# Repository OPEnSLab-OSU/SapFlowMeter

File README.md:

# SapFlowMeter

A sap flow meter measures the velocity of the sap in a tree. This is a useful indicator of the tree's health, and can provide valuable feedback for irrigation and water management.

Our meter here uses the Heat Ratio Method, where it applies a heat pulse into the sapwood, and measures the temperature of the sapwood both above and below the heater.

Currently we have designed flexible PCB probes, and we are testing our sap flow measurements in a tree against empirical water consumption measurements and a commercial sapflow probe.

## Libraries required:
- [SdFat](https://github.com/greiman/SdFat "SdFat")
- [OPEnS RTC](https://github.com/OPEnSLab-OSU/OPEnS_RTC "OPEnS_RTC")
- [Adafruit MAX31865](https://github.com/adafruit/Adafruit_MAX31865 "Adafruit MAX31865")
- [Low-Power](https://github.com/rocketscream/Low-Power "Low-Power")
- [Protothreads](https://github.com/P4SSER8Y/ProtoThreadsForArduino)
- [DSPlite](https://github.com/kamocat/DSPlite)
- [RadioHead](https://github.com/adafruit/RadioHead)
- [ArduinoJSON](https://github.com/bblanchon/ArduinoJson)
- [FeatherFault](https://github.com/OPEnSLab-OSU/FeatherFault)
- [ASF core](https://github.com/adafruit/Adafruit_ASFcore.git) commit f6ffa8b
- [Plog](https://github.com/OPEnSLab-OSU/plog)

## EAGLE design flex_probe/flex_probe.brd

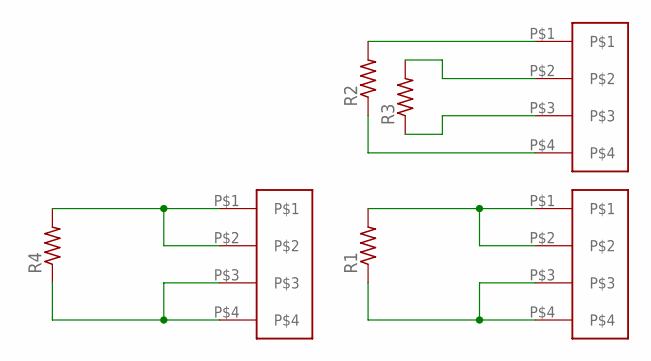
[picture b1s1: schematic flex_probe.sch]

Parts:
R1, R2, R3, R4: R-US_R0603; R0603
U$1, U$2, U$3: CONN_1X4; 4PAD

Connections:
unnamed: R1.2, U$1.P$1, U$1.P$2
unnamed: R1.1, U$1.P$3, U$1.P$4
unnamed: R2.1, U$2.P$4
unnamed: R3.2, U$2.P$2
unnamed: R3.1, U$2.P$3
unnamed: R2.2, U$2.P$1
unnamed: R4.2, U$3.P$1, U$3.P$2
unnamed: R4.1, U$3.P$3, U$3.P$4

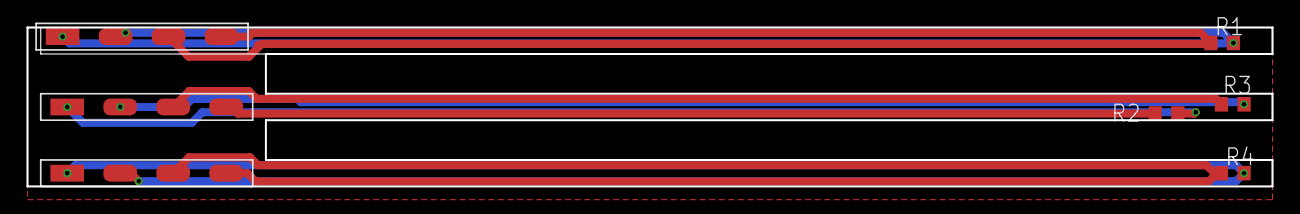
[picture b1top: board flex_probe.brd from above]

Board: 2 copper layers, 94.0 x 12.0 mm, 7 parts (0 on the bottom side), 8 nets.

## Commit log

2019-11-27 Deployed in tree 11/26/2019
    Currently testing quality of measurements and calculations.
2019-11-27 Update README.md
    Added "required libraries" list to readme
2019-11-27 Changed formula for flow calculation.
2019-11-27 Made Python script for examining data from sapflow probe
2019-11-27 Attempting to parse dates. Not working very well
2019-12-08 Made a least-squares slope finder
2019-12-08 Huge improvement in linear regression over naive slope
2019-12-08 Optimized linear regression for translation to C++
2019-12-08 Partial revert of 'optimization'.
    Numpy is much much faster than a for loop. Changed the for-loop accumulation back to a matrix dot-product.
2019-12-08 Put new calculation into a function.
    Intended to test for zeroing in on the steepest part of the slope,
    but it seemed to make slope estimates worse rather than better.
2019-12-10 Added 3rd RTD.
    Working on refactoring code to remvoe extra stuff
2019-12-26 Had to revert the changes to Adafruit's Max31965
2019-12-26 Logging weight successfully
2020-01-06 Use improved calculation to determine sapflow, and extract weight for comparison
2020-01-07 Added Adafruit's feather LoRa examples
2020-01-07 Reliable datagram over LoRa
2020-01-11 Made script to smooth the quantization error out of the weight measurement
2020-01-11 fixed discontinuities which occur during watering
2020-01-22 scaling weight to gravimetric
2020-01-31 Integrated JSON formatted LORA messages and Ethernet transmission to database
2020-02-01 Fixed issues with sapflow calculation
    - Excluded data while the heater probe is on. The heater still seems to present electrical conduction issues for the RTDs.
    - Included upper and lower slope and baseline in processed data. This is useful for determining what the issues are that are causing wonky sapflow results.
2020-02-05 Rewriting sapflow using protothreads
2020-02-06 Debugging protothreads
2020-02-06 Threading seems to work.
    Looks like the 5V line on the Hypnos failed again though
2020-02-06 Seems to be trouble with the thread spawning
2020-02-06 Fixed thread issue
    Apparently child threads should block, as yielding allows the parent to continue
2020-02-06 Forced SD card to log
    Had to flush the file every time. I think the sleep prep mechanism isn't working - maybe I should use a semaphore instead?
2020-02-06 Attempting to compartmentalize LoRa
2020-02-06 Compilation issues fixed.
    Needs testing
2020-02-06 Merged LoRa into protothreads sketch
    I sure hope it works.
2020-02-06 Demo for OPEnS lab open house
2020-02-07 Fixed measurement bug
2020-02-08 Still having issues with weight.
2020-02-09 Added Doxygen documentation
2020-02-09 Resolved Doxygen warnings
    All functions, parameters, and globals are documented
2020-02-13 Missed an end parenthesis
2020-02-16 Added maxtemp
    Disabled sleep, started sending actual time
2020-02-18 Added additional comments for debugging
2020-02-18 Modified log to open and close every time.
    Administrative changes:
    Removed elf and bin files from commit.
    Added Makefile for arduino-cli
2020-02-19 Moved location of html files
2020-02-19 Added mainpage for doxygen
2020-02-19 added main page
2020-02-19 Modified doxygen image to use relative path
2020-02-19 Testing relative image path
2020-02-19 Adding pictures
2020-02-19 Reverting to previous relative image path style
2020-02-19 Trying previous path style again
2020-02-19 Created sketch to test watchdog debugging
2020-02-19 Watchdog works, but seems to have scope issues
2020-02-19 Set watchdog to hard reset after two interrupt periods
2020-02-20 Moved variables from inside class to global scope - works now
2020-02-20 Fixed debug saving and restoring
2020-02-20 Watchdog reset works properly
2020-02-20 Added debug tags
2020-02-20 Implemented watchdog on sapflow_protothread
2020-02-20 Fixed maxtemp
2020-02-20 Started reading halt location at every wake
2020-02-21 Disabled waiting for serial
2020-02-27 Updated required libraries in README
2020-02-27 Removed extra repositories.
    Hardware design has moved to the [OPEnS Hardware Repository](https://github.com/OPEnSLab-OSU/PCB)
2020-02-27 Improved documentation
2020-02-27 Removed test project for watchdog debug
2020-02-27 Update index.html
    Fixed redirect page
2020-03-02 Added another commit in hopes that gh-pages will work
2020-03-06 Switched to FeatherFault
2020-03-07 Updated Makefile with "recover" option
2020-03-10 innitial commit - code untested
2020-03-13 Included FeatherFault in LoRa base station
2020-03-13 Removed some bulk from LoRa base station. Program is timing out during 'Ethernet.begin'
2020-03-13 Turned down the heat pulse
2020-03-13 Simplified MCP example
2020-03-13 Simplified temperature conversion.
    Lower and Heater probes seem to measure within 0.3 degrees of each other. The Upper Probe is constantly reading 0 - probably a bug in the data storage
2020-03-13 All three temperatures look correct now.
    I changed the output to show drift in millidegrees, so we can see something comparable to the measurements in a tree.
2020-03-15 Turned on 3.3 and 5v rails
2020-03-16 MCP3424 example now uses protothreads. Compiles but needs testing.
2020-03-16 Refactoring to allow multiple instances of a protothread
2020-03-16 Fixed typos
2020-03-17 Heater and Upper probes were swapped on MCP3424 example
2020-03-17 Testing multiple probes on one datalogger
    Having issues with spawned threads looping after exiting. Might need to use a rendezvous.
2020-03-17 Multiple probes working one one datalogger
2020-03-19 rhody deployment test
2020-03-19 Updated documentation
    Removed inline sources and verbatim headers
2020-03-20 Added .gitignore
2020-03-23 Fixed issue of hanging on wakeup
2020-03-24 Added jupyter notebook for examining tree data
2020-03-24 Created data folder
2020-03-25 Added Burgess HRM method
2020-03-25 Started linear regression method.
    Decided tree3.csv didn't have any data worth keeping
2020-03-26 Timer (#4)
    Implemented sleep_cycle() delay to avoid LoRa packet collisions via TDMA
2020-04-19 Using Plog for system error logging
2020-04-19 Swapped upper and lower due to hardware change
    Also added a second probe
2020-04-20 Re-enabled LoRa
    Now uses PLOG for logging messages
2020-04-25 Simplified configuration steps for multiple probes
    Sleep offset is now automatically calculated based off the maximum treeID
    Measurement threads with a treeID of 0 will now do nothing (allowing a convenient way to disable threads)
    LoRa radio switched to regular transmit/receive rather than ReliableDatagram
2020-04-30 Relaxed watchdog requirements
    Watchdog timer is increased to 4 seconds.
    Schedule now sleeps immidiately, so repeated watchdog faults shouldn't kill the battery.
    Fixed sleep.cpp to log with plog rather than cout.
2020-05-01 Tested new data from field deployment
2020-05-03 Added notes about data
2020-05-05 Added new data
2020-05-05 Moved jupyter notebooks to its own folder
2020-05-05 Inspected tree1 data
2020-06-14 Updated README.md to include Plog dependency
2021-07-30 Relaxed Watchdog
    Watchdog commented out.
2021-07-30 Remove LoRa Call
    As we are not using LoRa currently, removing the initialization and message creation and sending saves time and power.
2021-07-30 Updated Dependency
2021-07-30 Single Probe Version
    Created a version made for use with a single probe, this is what is currently deployed in the field and is verified to work. Progress and development on a two probe system has been paused for the mea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
2021-07-30 Rename sapflow_protothread.ino to sapflow_protothread_2probe.ino
2021-07-30 Single Probe Ver of Sapflow protothread
    Created a single probe version of the Sapflow Protothread as this is the one that is currently bein used in the field. The dual probe system is currently paused as it doesn't work and we are focusing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
2021-11-05 Sapflow with Battery Monitoring and RGB Debug
    A new version of the code base for the Ver 6 of the Sapflow Wing, entailing the LTC2943 Battery Monitoring, the switch for automatically turning off the device, and RGB Led.
